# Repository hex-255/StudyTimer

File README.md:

# StudyTimer
study timer with neopixel feedback and adaptive break time calculation

study for amount of time you decide and get break time allotted accordingly. 

break time = time studied divided by 5

formfactor inspired by [Adafruit NeoPixel rotary fidget](https://learn.adafruit.com/neopixel-rotary-fidget/overview) 

Check out the the [Instructables article](https://www.instructables.com/MagSafe-StudyTimer-Makes-Studying-3-More-Enjoyable/) for an in-depth build guide.

## Features
- Neopixel visual feedback (one pixel equals 2.5 minutes of study time or 1 minute of breaktime)
- Adaptive break time calculation
- Audio feedback with mini speaker
- interface through [Adafruit ANO Rotary Encoder](https://learn.adafruit.com/ano-rotary-encoder)

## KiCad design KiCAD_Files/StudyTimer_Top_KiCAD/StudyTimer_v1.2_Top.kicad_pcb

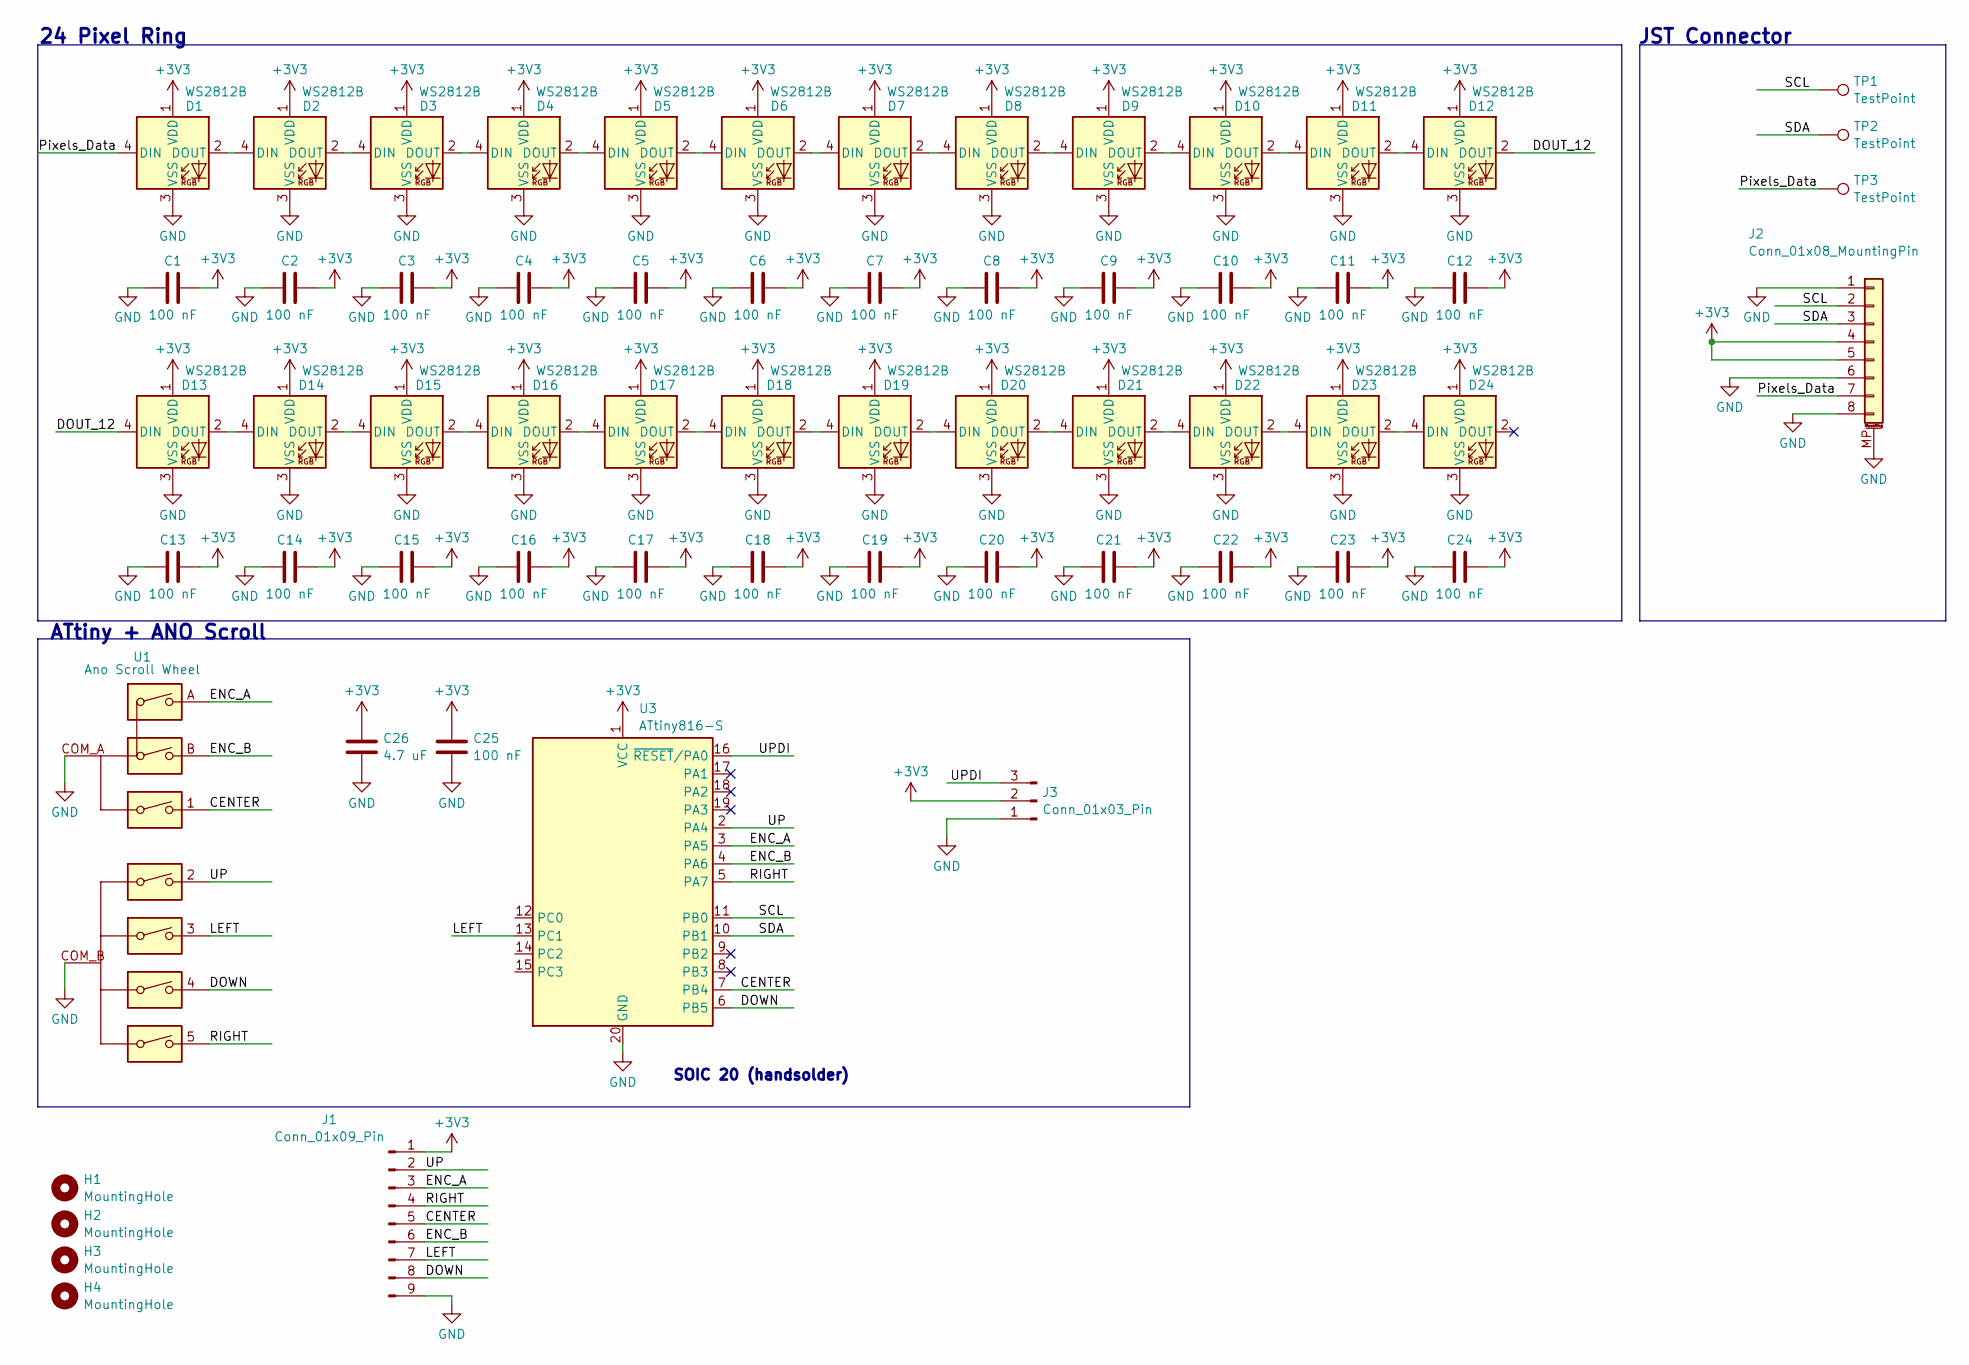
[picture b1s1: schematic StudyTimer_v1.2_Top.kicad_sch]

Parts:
C1, C2, C3, C4, C5, C6, C7, C8, C9, C10, C11, C12, C13, C14, C15, C16, C17, C18, C19, C20, C21, C22, C23, C24, C25: 100 nF; C_0805_2012Metric_Pad1.18x1.45mm_HandSolder
C26: 4.7 uF; C_0805_2012Metric_Pad1.18x1.45mm_HandSolder
D1: WS2812B; LED_WS2812B_PLCC4_5.0x5.0mm_P3.2mm_edited; Manufacturer_Part_Number 3094
D2, D3, D4, D5, D6, D7, D8, D9, D10, D11, D12, D13, D14, D15, D16, D17, D18, D19, D20, D21, D22, D23, D24: WS2812B; LED_WS2812B_PLCC4_5.0x5.0mm_P3.2mm_edited
H1, H2, H3, H4: MountingHole; MountingHole_3.2mm_M3
J1: Conn_01x09_Pin; PinHeader_1x09_P2.54mm_Vertical
J2: Conn_01x08_MountingPin; SM08BSRSSTBLFSN_1mm_8Pin; Manufacturer_Part_Number SM08B-SRSS-TB
J3: Conn_01x03_Pin; PinHeader_1x03_P2.54mm_Vertical
TP1, TP2, TP3: TestPoint; TestPoint_THTPad_D2.0mm_Drill1.0mm
U1: Ano Scroll Wheel; ANO Scroll Wheel; Manufacturer_Part_Number 5001
U3: ATtiny816-S; SOIC-20W_7.5x12.8mm_P1.27mm; Manufacturer_Part_Number ATTINY816-SNR

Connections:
+3V3: C1.2, C2.2, C3.2, C4.2, C5.2, C6.2, C7.2, C8.2, C9.2, C10.2, C11.2, C12.2, C13.2, C14.2, C15.2, C16.2, C17.2, C18.2, C19.2, C20.2, C21.2, C22.2, C23.2, C24.2, C25.1, C26.1, D1.1 (VDD), D2.1 (VDD), D3.1 (VDD), D4.1 (VDD), D5.1 (VDD), D6.1 (VDD), D7.1 (VDD), D8.1 (VDD), D9.1 (VDD), D10.1 (VDD), D11.1 (VDD), D12.1 (VDD), D13.1 (VDD), D14.1 (VDD), D15.1 (VDD), D16.1 (VDD), D17.1 (VDD), D18.1 (VDD), D19.1 (VDD), D20.1 (VDD), D21.1 (VDD), D22.1 (VDD), D23.1 (VDD), D24.1 (VDD), J1.1, J2.4, J2.5, J3.2, U3.1 (VCC)
/CENTER: J1.5, U1.1, U3.7 (PB4)
/DOUT_12: D12.2 (DOUT), D13.4 (DIN)
/DOWN: J1.8, U1.4, U3.6 (PB5)
/ENC_A: J1.3, U1.A, U3.3 (PA5)
/ENC_B: J1.6, U1.B, U3.4 (PA6)
/LEFT: J1.7, U1.3, U3.13 (PC1)
/Pixels_Data: D1.4 (DIN), J2.7, TP3.1
/RIGHT: J1.4, U1.5, U3.5 (PA7)
/SCL: J2.2, TP1.1, U3.11 (PB0)
/SDA: J2.3, TP2.1, U3.10 (PB1)
/UP: J1.2, U1.2, U3.2 (PA4)
/UPDI: J3.3, U3.16 (~RESET/PA0)
GND: C1.1, C2.1, C3.1, C4.1, C5.1, C6.1, C7.1, C8.1, C9.1, C10.1, C11.1, C12.1, C13.1, C14.1, C15.1, C16.1, C17.1, C18.1, C19.1, C20.1, C21.1, C22.1, C23.1, C24.1, C25.2, C26.2, D1.3 (VSS), D2.3 (VSS), D3.3 (VSS), D4.3 (VSS), D5.3 (VSS), D6.3 (VSS), D7.3 (VSS), D8.3 (VSS), D9.3 (VSS), D10.3 (VSS), D11.3 (VSS), D12.3 (VSS), D13.3 (VSS), D14.3 (VSS), D15.3 (VSS), D16.3 (VSS), D17.3 (VSS), D18.3 (VSS), D19.3 (VSS), D20.3 (VSS), D21.3 (VSS), D22.3 (VSS), D23.3 (VSS), D24.3 (VSS), J1.9, J2.1, J2.6, J2.8, J2.MP (MountPin), J3.1, U1.COM_A, U1.COM_B, U3.20 (GND)
unnamed: D1.2 (DOUT), D2.4 (DIN)
unnamed: D2.2 (DOUT), D3.4 (DIN)
unnamed: D3.2 (DOUT), D4.4 (DIN)
unnamed: D4.2 (DOUT), D5.4 (DIN)
unnamed: D5.2 (DOUT), D6.4 (DIN)
unnamed: D6.2 (DOUT), D7.4 (DIN)
unnamed: D7.2 (DOUT), D8.4 (DIN)
unnamed: D8.2 (DOUT), D9.4 (DIN)
unnamed: D9.2 (DOUT), D10.4 (DIN)
unnamed: D10.2 (DOUT), D11.4 (DIN)
unnamed: D11.2 (DOUT), D12.4 (DIN)
unnamed: D13.2 (DOUT), D14.4 (DIN)
unnamed: D14.2 (DOUT), D15.4 (DIN)
unnamed: D15.2 (DOUT), D16.4 (DIN)
unnamed: D16.2 (DOUT), D17.4 (DIN)
unnamed: D17.2 (DOUT), D18.4 (DIN)
unnamed: D18.2 (DOUT), D19.4 (DIN)
unnamed: D19.2 (DOUT), D20.4 (DIN)
unnamed: D20.2 (DOUT), D21.4 (DIN)
unnamed: D21.2 (DOUT), D22.4 (DIN)
unnamed: D22.2 (DOUT), D23.4 (DIN)
unnamed: D23.2 (DOUT), D24.4 (DIN)

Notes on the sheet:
ATtiny + ANO Scroll
JST Connector
SOIC 20 (handsolder)
24 Pixel Ring

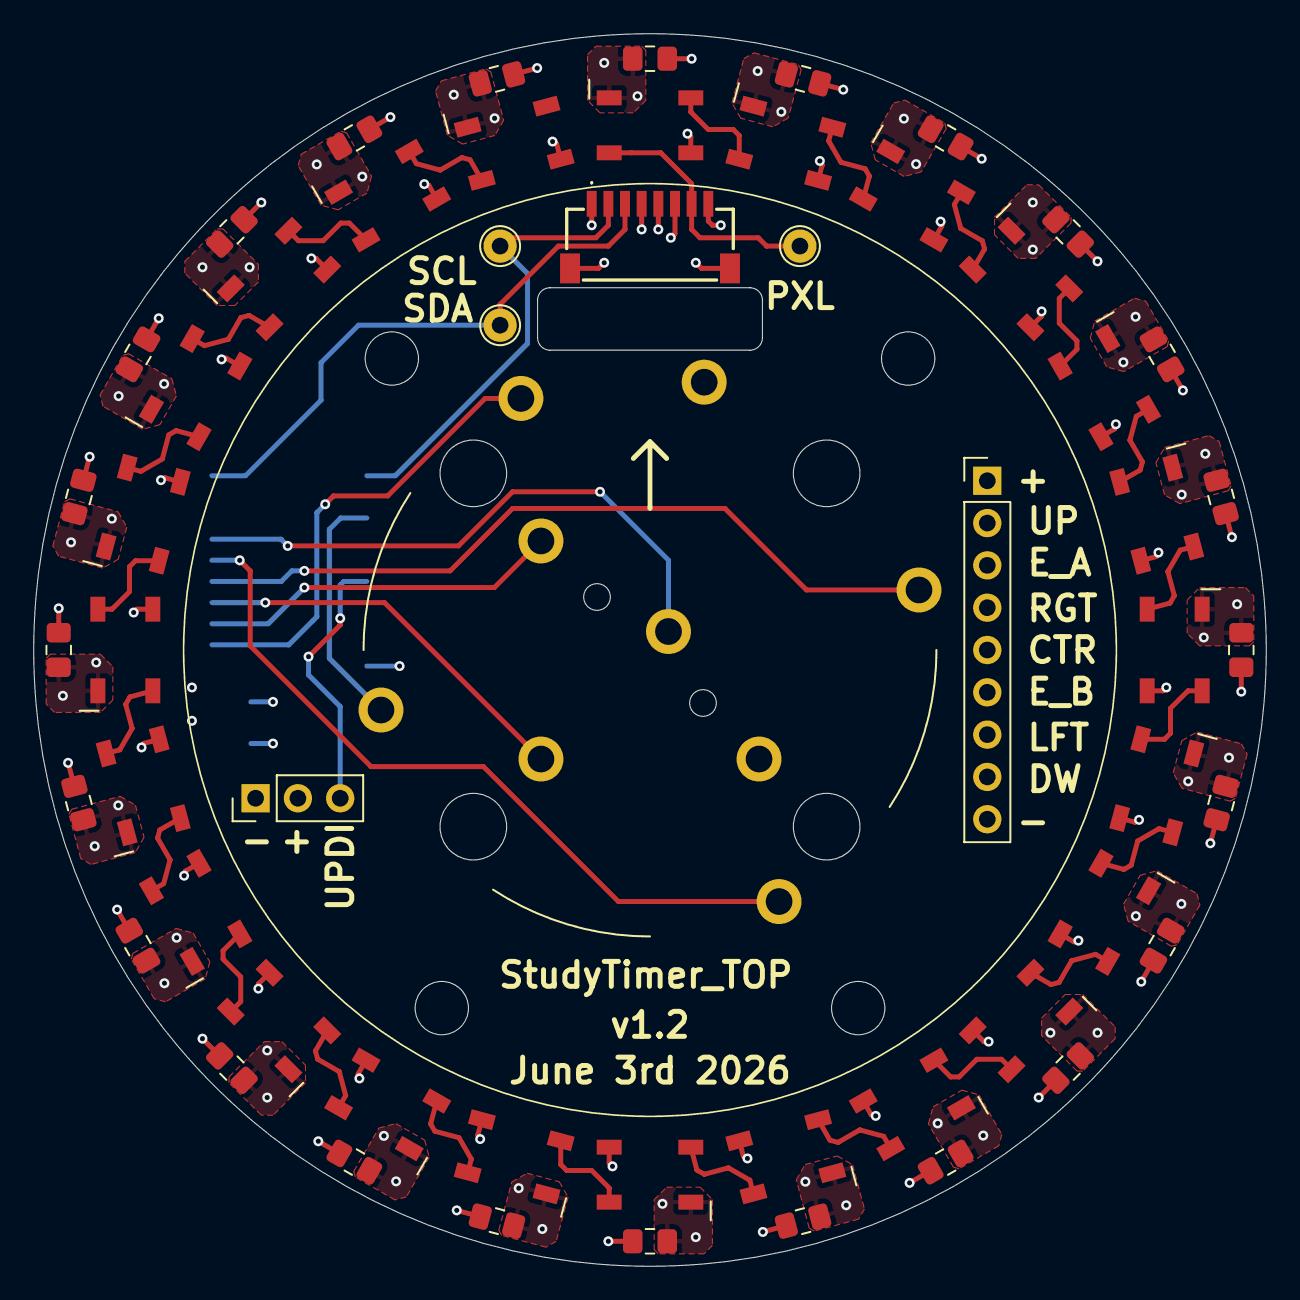
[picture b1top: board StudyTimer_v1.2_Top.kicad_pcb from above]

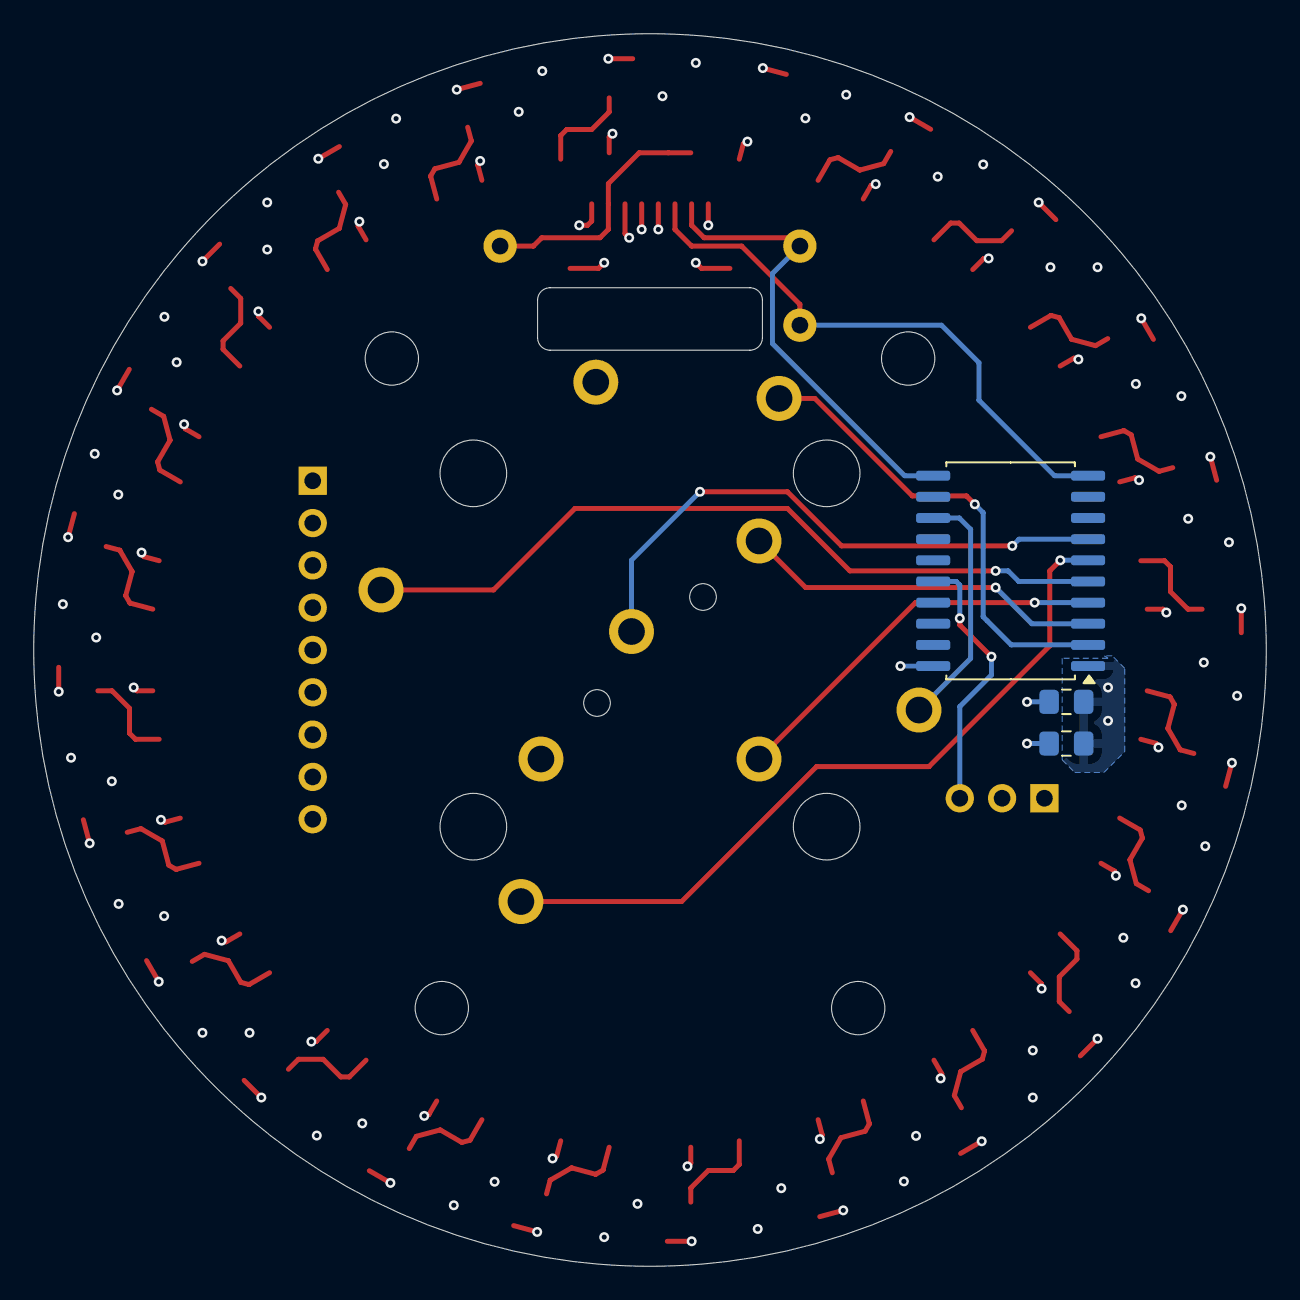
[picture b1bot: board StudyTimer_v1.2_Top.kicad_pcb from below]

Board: 4 copper layers, 74.0 x 74.0 mm, 62 parts (3 on the bottom side), 36 nets.

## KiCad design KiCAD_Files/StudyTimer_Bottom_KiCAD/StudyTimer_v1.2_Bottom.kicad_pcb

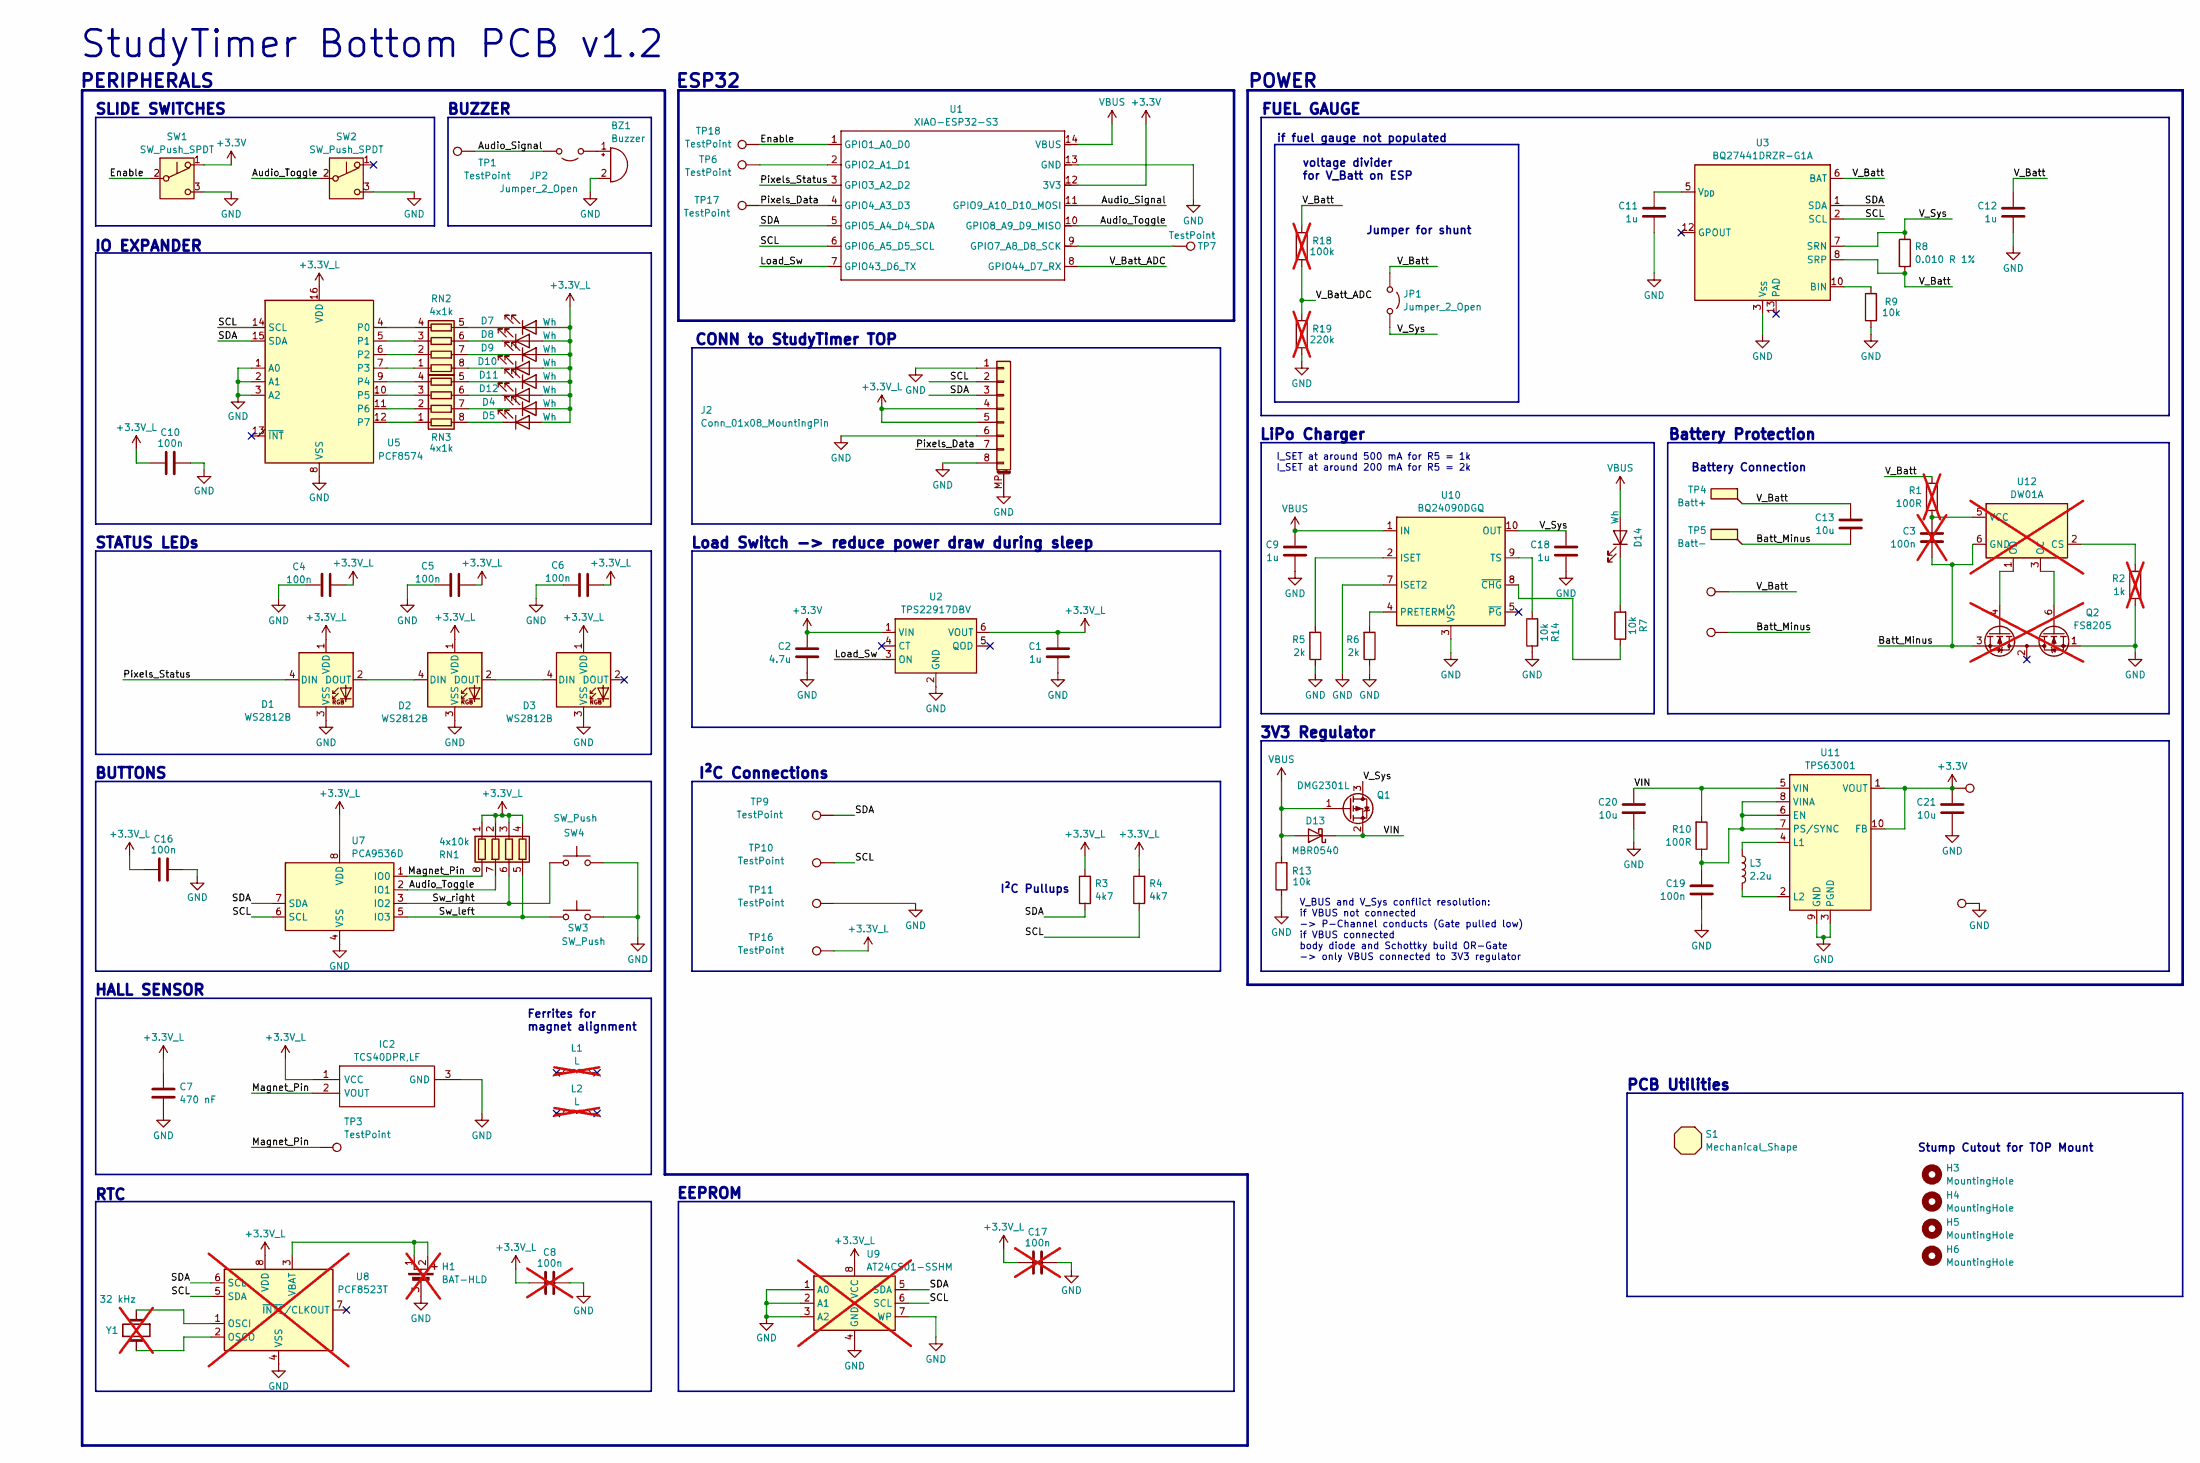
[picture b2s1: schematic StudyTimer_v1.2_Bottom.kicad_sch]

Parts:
BZ1: Buzzer; Buzzer_CUI_CPT-9019S-SMT; Manufacturer_Part_Number CPT-9019S-SMT-TR
C1, C9, C11, C12, C18: 1u; C_0805_2012Metric_Pad1.18x1.45mm_HandSolder
C2: 4.7u; C_0805_2012Metric_Pad1.18x1.45mm_HandSolder
C3, C8, C17: 100n; C_0805_2012Metric_Pad1.18x1.45mm_HandSolder; not fitted
C4, C5, C6, C10, C16, C19: 100n; C_0805_2012Metric_Pad1.18x1.45mm_HandSolder
C7: 470 nF; C_0805_2012Metric_Pad1.18x1.45mm_HandSolder
C13, C20, C21: 10u; C_0805_2012Metric_Pad1.18x1.45mm_HandSolder
D1, D2, D3: WS2812B; LED_WS2812B_PLCC4_5.0x5.0mm_P3.2mm
D4, D5, D8, D9, D10, D11, D12, D14: Wh; LED_0805_2012Metric_Pad1.15x1.40mm_HandSolder
D7: Wh; LED_0805_2012Metric_Pad1.15x1.40mm_HandSolder; Manufacturer_Part_Number IN-S85AT5UW
D13: MBR0540; D_SOD-123
H1: BAT-HLD; BATHLD007SMTTR; Manufacturer_Part_Number BAT-HLD-003-SMT; Mouser Part Number 712-BAT-HLD-003-SMT; not fitted
H3, H4, H5, H6: MountingHole; StudyTimer_Stump_Cutout
IC2: TCS40DPR,LF; SOTFL95P240X88-3N; Manufacturer_Part_Number TCS40DPR,LF; Mouser Part Number 757-TCS40DPRLF
J2: Conn_01x08_MountingPin; BM08BSRSSTBLFSN; Manufacturer_Part_Number BQ27441DRZR-G1A
JP1, JP2: Jumper_2_Open; SolderJumper-2_P1.3mm_Open_TrianglePad1.0x1.5mm
L1, L2: L; INDPM4341X80N; not fitted
L3: 2.2u; L_1008_2520Metric_Pad1.43x2.20mm_HandSolder
Q1: DMG2301L; SOT-23
Q2: FS8205; SOT-23-6; not fitted
R1: 100R; R_0805_2012Metric_Pad1.20x1.40mm_HandSolder; not fitted
R2: 1k; R_0805_2012Metric_Pad1.20x1.40mm_HandSolder; not fitted
R3, R4: 4k7; R_0805_2012Metric_Pad1.20x1.40mm_HandSolder
R5, R6: 2k; R_0805_2012Metric_Pad1.20x1.40mm_HandSolder
R7, R9, R13, R14: 10k; R_0805_2012Metric_Pad1.20x1.40mm_HandSolder
R8: 0.010 R 1%; R_0805_2012Metric_Pad1.20x1.40mm_HandSolder; Manufacturer_Part_Number CRF0805-FZ-R010ELF
R10: 100R; R_0805_2012Metric_Pad1.20x1.40mm_HandSolder
R18: 100k; R_0805_2012Metric_Pad1.20x1.40mm_HandSolder; not fitted
R19: 220k; R_0805_2012Metric_Pad1.20x1.40mm_HandSolder; not fitted
RN1: 4x10k; R_Array_Convex_4x0612; Manufacturer_Part_Number ACASA100221002P100
RN2, RN3: 4x1k; R_Array_Convex_4x0612; Manufacturer_Part_Number ACASA100121001P100
S1: Mechanical_Shape; Outline_StudyTimer_v1.2
SW1, SW2: SW_Push_SPDT; SS12SDH2; Manufacturer_Part_Number SS12SDH2
SW3: SW_Push; KSS341G LFS
SW4: SW_Push; KSS341G LFS; Manufacturer_Part_Number KSS341G LFS
TP1, TP2, TP6, TP7, TP9, TP10, TP11, TP12, TP16, TP17, TP18: TestPoint; TestPoint_THTPad_D2.0mm_Drill1.0mm
TP3: TestPoint; TestPoint_Pad_2.0x2.0mm
TP4: Batt+; TestPoint_Pad_2.5x2.5mm
TP5: Batt-; TestPoint_Pad_2.5x2.5mm
TP14, TP21: TestPoint; TestPoint_THTPad_D1.5mm_Drill0.7mm
U1: XIAO-ESP32-S3; XIAO-ESP32-S3-SMD; Manufacturer_Part_Number 113991114
U2: TPS22917DBV; SOT-23-6; Manufacturer_Part_Number TPS22917DBVT
U3: BQ27441DRZR-G1A; Texas_S-PDSO-N12; Manufacturer_Part_Number BQ27441DRZR-G1A
U5: PCF8574; SOIC-16W_7.5x10.3mm_P1.27mm; Manufacturer_Part_Number PCF8574ADWR
U7: PCA9536D; SOIC-8_3.9x4.9mm_P1.27mm; Manufacturer_Part_Number PCA9536DR
U8: PCF8523T; SOIC-8_3.9x4.9mm_P1.27mm; not fitted
U9: AT24CS01-SSHM; SOIC-8_3.9x4.9mm_P1.27mm; not fitted
U10: BQ24090DGQ; HVSSOP-10-1EP_3x3mm_P0.5mm_EP1.83x1.89mm_ThermalVias; Manufacturer_Part_Number BQ24090DGQT
U11: TPS63001; Texas_DRC0010J_ThermalVias; Manufacturer_Part_Number TPS63001DRCR
U12: DW01A; SOT-23-6; not fitted
Y1: 32 kHz; ABS2532768KHZT; not fitted

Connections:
+3.3V: C2.2, C21.2, SW1.1 (A), TP21.1, U1.12 (3V3), U2.1 (VIN), U11.1 (VOUT), U11.10 (FB)
+3.3V_L: C1.2, C4.2, C5.2, C6.2, C7.1, C8.1, C10.1, C16.1, C17.1, D1.1 (VDD), D2.1 (VDD), D3.1 (VDD), D4.2 (A), D5.2 (A), D7.2 (A), D8.2 (A), D9.2 (A), D10.2 (A), D11.2 (A), D12.2 (A), IC2.1 (VCC), J2.4, J2.5, R3.2, R4.2, RN1.1 (R1.1), RN1.2 (R2.1), RN1.3 (R3.1), RN1.4 (R4.1), TP16.1, U2.6 (VOUT), U5.16 (VDD), U7.8 (VDD), U8.8 (VDD), U9.8 (VCC)
/Audio_Signal: JP2.2 (B), TP1.1, U1.11 (GPIO9_A10_D10_MOSI)
/Audio_Toggle: RN1.7 (R2.2), SW2.2 (B), U1.10 (GPIO8_A9_D9_MISO), U7.2 (IO1)
/Batt_Minus: C3.1, C13.1, Q2.3 (S2), TP5.1, TP12.1, U12.6 (GND)
/Enable: SW1.2 (B), TP18.1, U1.1 (GPIO1_A0_D0)
/Load_Sw: U1.7 (GPIO43_D6_TX), U2.3 (ON)
/Magnet_Pin: IC2.2 (VOUT), RN1.8 (R1.2), TP3.1, U7.1 (IO0)
/Pixels_Data: J2.7, TP17.1, U1.4 (GPIO4_A3_D3)
/Pixels_Status: D1.4 (DIN), U1.3 (GPIO3_A2_D2)
/SCL: J2.2, R4.1, TP10.1, U1.6 (GPIO6_A5_D5_SCL), U3.2 (SCL), U5.14 (SCL), U7.6 (SCL), U8.5 (SDA), U9.6 (SCL)
/SDA: J2.3, R3.1, TP9.1, U1.5 (GPIO5_A4_D4_SDA), U3.1 (SDA), U5.15 (SDA), U7.7 (SDA), U8.6 (SCL), U9.5 (SDA)
/Sw_left: RN1.5 (R4.2), SW3.1, U7.5 (IO3)
/Sw_right: RN1.6 (R3.2), SW4.1, U7.3 (IO2)
/VIN: C20.2, D13.1 (K), Q1.2 (S), R10.2, U11.5 (VIN)
/V_Batt: C12.2, C13.2, JP1.1 (A), R1.2, R8.2, R18.2, TP2.1, TP4.1, U3.6 (BAT), U3.8 (SRP)
/V_Batt_ADC: R18.1, R19.2, U1.8 (GPIO44_D7_RX)
/V_Sys: C18.2, JP1.2 (B), Q1.3 (D), R8.1, U3.7 (SRN), U10.10 (OUT)
GND: BZ1.2 (-), C1.1, C2.1, C4.1, C5.1, C6.1, C7.2, C8.2, C9.1, C10.2, C11.1, C12.1, C16.2, C17.2, C18.1, C19.1, C20.1, C21.1, D1.3 (VSS), D2.3 (VSS), D3.3 (VSS), H1.3, IC2.3 (GND), J2.1, J2.6, J2.8, J2.MP (MountPin), Q2.1 (D1), R2.1, R5.1, R6.1, R9.1, R13.1, R14.1, R19.1, SW1.3 (C), SW2.3 (C), SW3.2, SW4.2, TP11.1, TP14.1, U1.13 (GND), U2.2 (GND), U3.3 (V_{SS}), U5.1 (A0), U5.2 (A1), U5.3 (A2), U5.8 (VSS), U7.4 (VSS), U8.4 (VSS), U9.1 (A0), U9.2 (A1), U9.3 (A2), U9.4 (GND), U9.7 (WP), U10.3 (VSS), U10.7 (ISET2), U10.11 (VSS), U11.3 (PGND), U11.9 (GND), U11.11 (PGND); also elsewhere on the board
unnamed: BZ1.1 (+), JP2.1 (A)
unnamed: D1.2 (DOUT), D2.4 (DIN)
unnamed: D2.2 (DOUT), D3.4 (DIN)
unnamed: D4.1 (K), RN3.7 (R2.2)
unnamed: D5.1 (K), RN3.8 (R1.2)
unnamed: D7.1 (K), RN2.5 (R4.2)
unnamed: D8.1 (K), RN2.6 (R3.2)
unnamed: D9.1 (K), RN2.7 (R2.2)
unnamed: D10.1 (K), RN2.8 (R1.2)
unnamed: D11.1 (K), RN3.5 (R4.2)
unnamed: D12.1 (K), RN3.6 (R3.2)
unnamed: D14.1 (K), R7.2
unnamed: Q2.6 (G1), U12.3 (OC)
unnamed: Q2.4 (G2), U12.1 (OD)
unnamed: RN2.1 (R1.1), U5.7 (P3)
unnamed: RN2.2 (R2.1), U5.6 (P2)
unnamed: RN2.3 (R3.1), U5.5 (P1)
unnamed: RN2.4 (R4.1), U5.4 (P0)
unnamed: RN3.1 (R1.1), U5.12 (P7)
unnamed: RN3.2 (R2.1), U5.11 (P6)
unnamed: RN3.3 (R3.1), U5.10 (P5)
unnamed: RN3.4 (R4.1), U5.9 (P4)
unnamed: TP6.1, U1.2 (GPIO2_A1_D1)
unnamed: TP7.1, U1.9 (GPIO7_A8_D8_SCK)
unnamed: R9.2, U3.10 (BIN)
unnamed: C11.2, U3.5 (V_{DD})
unnamed: U8.1 (OSCI), Y1.1
unnamed: U8.2 (OSCO), Y1.2
unnamed: H1.1, H1.2, U8.3 (VBAT)
unnamed: R5.2, U10.2 (ISET)
unnamed: R6.2, U10.4 (PRETERM)
unnamed: R14.2, U10.9 (TS)
unnamed: R7.1, U10.8 (~CHG)
unnamed: C19.2, R10.1, U11.6 (EN), U11.7 (PS/SYNC), U11.8 (VINA)
unnamed: L3.1, U11.4 (L1)
unnamed: L3.2, U11.2 (L2)
unnamed: R2.2, U12.2 (CS)
unnamed: C3.2, R1.1, U12.5 (VCC)
VBUS: C9.2, D13.2 (A), D14.2 (A), Q1.1 (G), R13.2, U1.14 (VBUS), U10.1 (IN)

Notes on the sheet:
IO EXPANDER
I²C Pullups
BUTTONS
Battery Connection
PERIPHERALS
Ferrites for magnet alignment
I_SET at around 500 mA for R5 = 1k I_SET at around 200 mA for R5 = 2k
ESP32
FUEL GAUGE
Load Switch -> reduce power draw during sleep
Battery Protection
if fuel gauge not populated
voltage divider for V_Batt on ESP
RTC
POWER
LiPo Charger
PCB Utilities
3V3 Regulator
EEPROM
STATUS LEDs
StudyTimer Bottom PCB v1.2
HALL SENSOR
V_BUS and V_Sys conflict resolution: if VBUS not connected -> P-Channel conducts (Gate pulled low) if VBUS connected body diode and Schottky build OR-Gate -> only VBUS connected to 3V3 regulator
Stump Cutout for TOP Mount
Jumper for shunt
I²C Connections
SLIDE SWITCHES
BUZZER
CONN to StudyTimer TOP

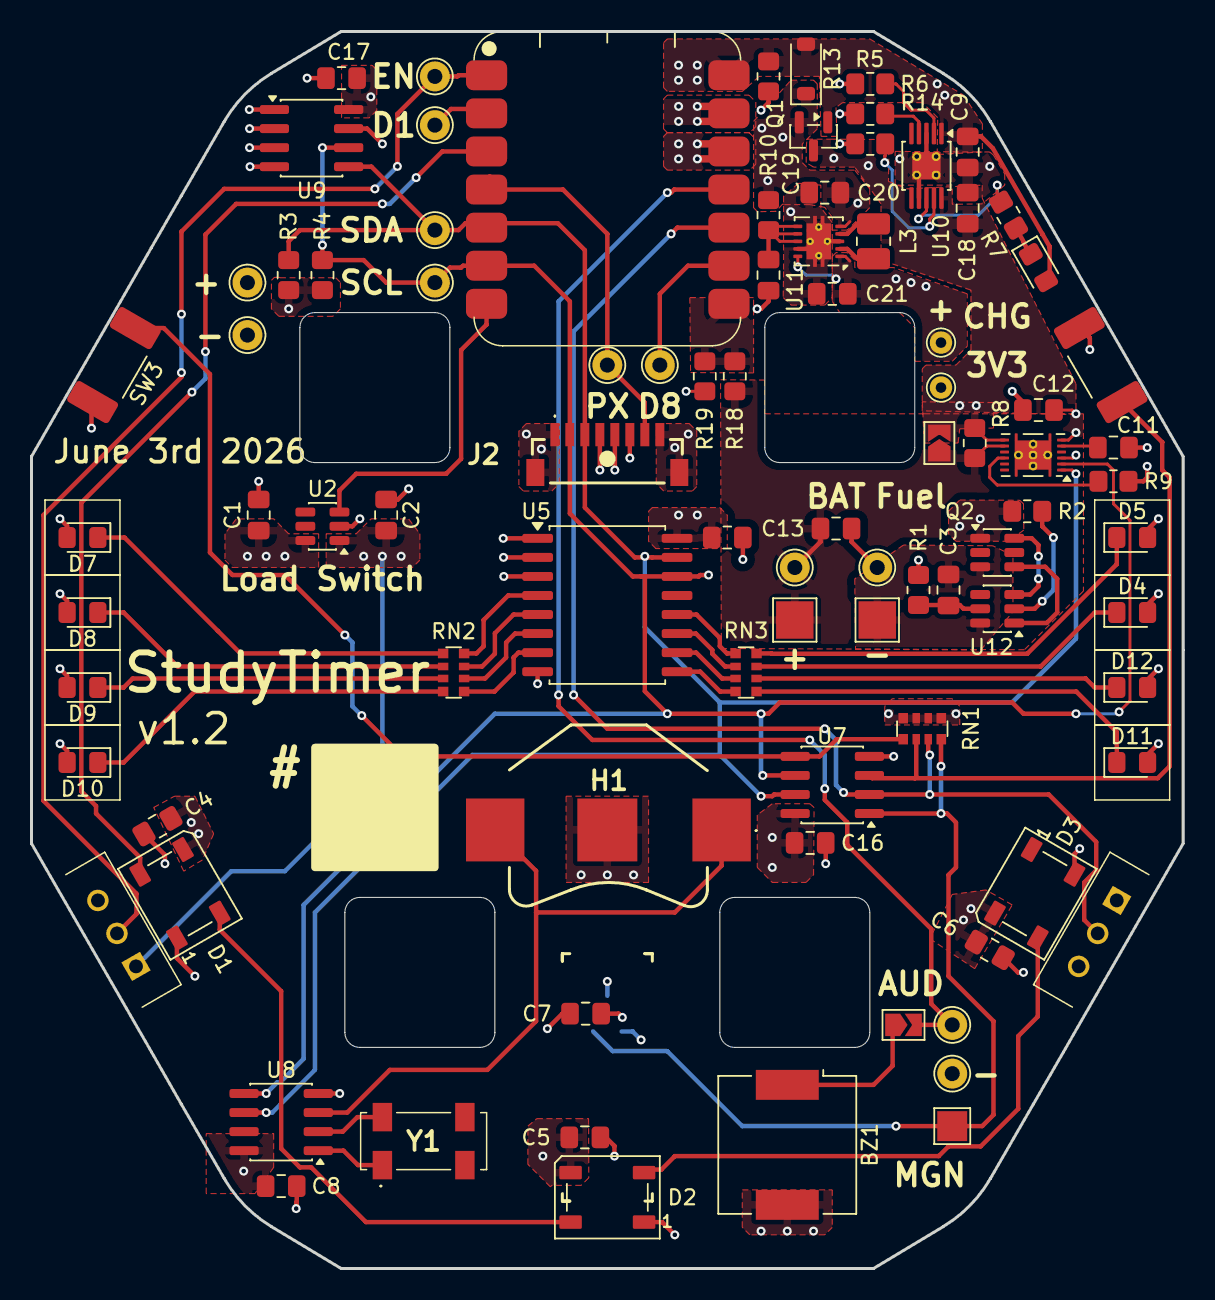
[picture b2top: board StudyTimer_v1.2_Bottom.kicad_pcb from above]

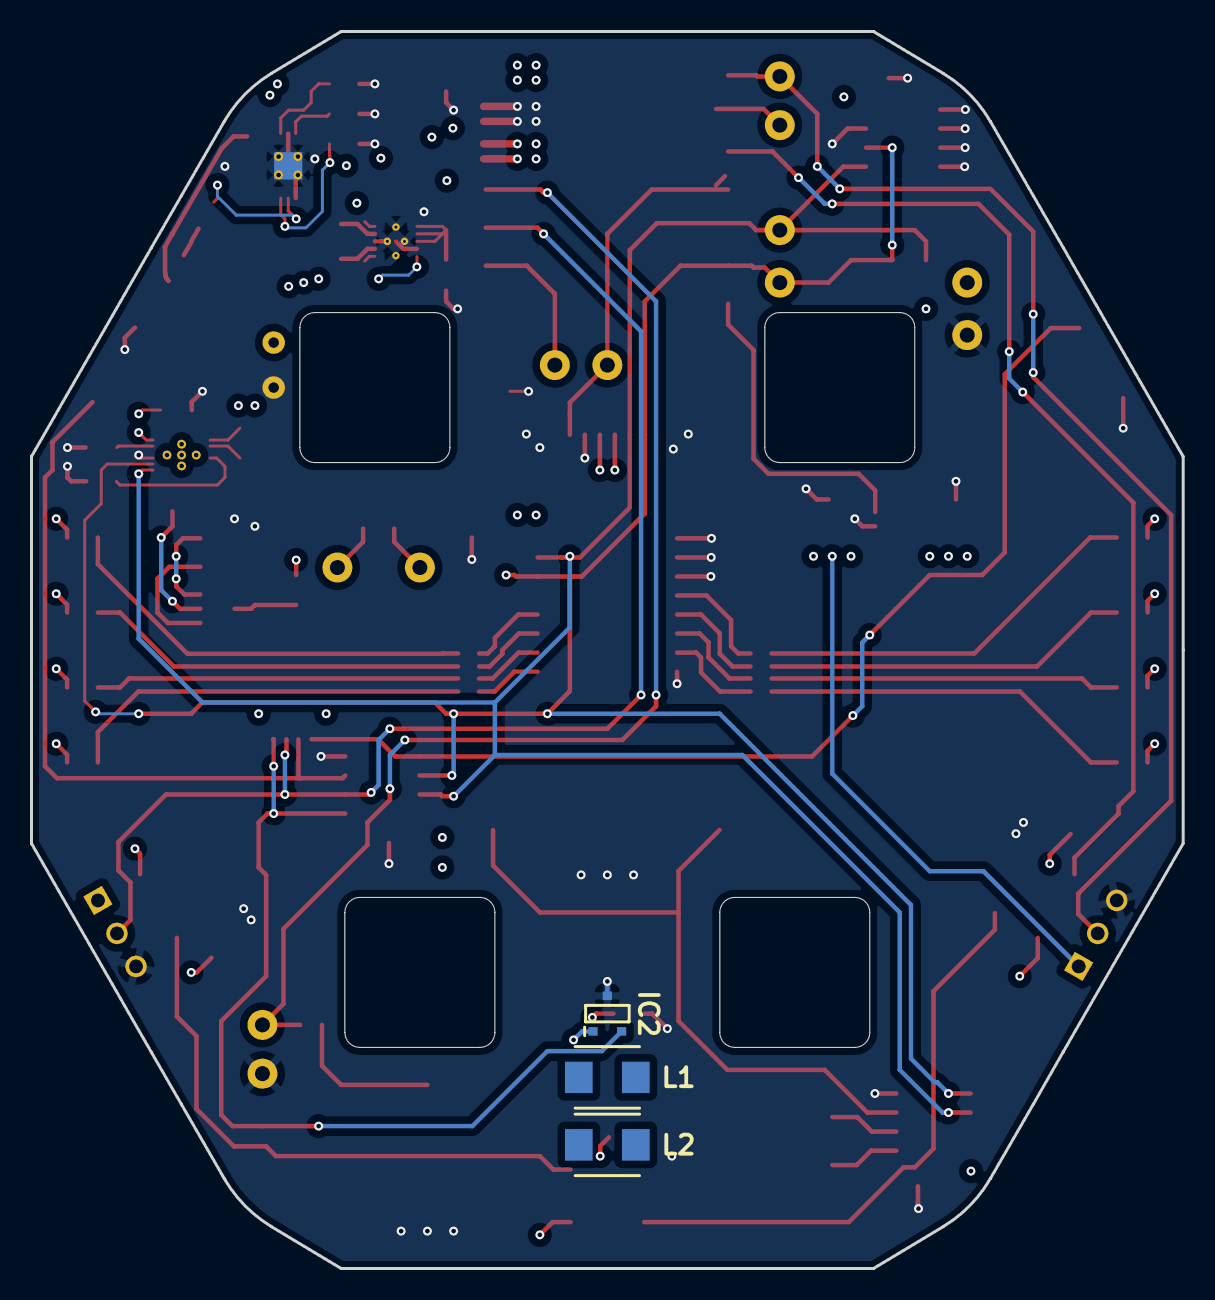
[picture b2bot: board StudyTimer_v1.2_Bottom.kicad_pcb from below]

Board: 4 copper layers, 76.8 x 82.5 mm, 97 parts (3 on the bottom side), 58 nets.

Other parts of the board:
TP13: TestPoint; TestPoint_THTPad_D2.0mm_Drill1.0mm

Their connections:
GND: TP13.1; also elsewhere on the board

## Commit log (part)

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2026-03-02 Update README.md
    added description for user interface
2026-06-27 Create ESP32 Firmware
2026-06-27 ESP32 firmware from PlatformIO
2026-06-27 KiCAD files for BOTTOM
2026-06-27 KiCAD files for TOP
2026-06-27 BOM files
2026-06-27 Gerber files for TOP and BOT board
2026-06-27 STL files for 3D printing
2026-06-27 firmware to be uploaded to ATTINY816 Seesaw
2026-06-27 Fusion Model of StudyTimer
2026-06-27 Clean up README for v1.2 added picture
